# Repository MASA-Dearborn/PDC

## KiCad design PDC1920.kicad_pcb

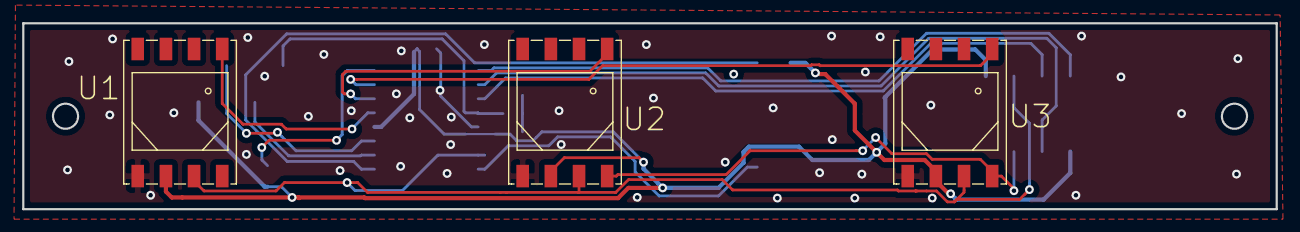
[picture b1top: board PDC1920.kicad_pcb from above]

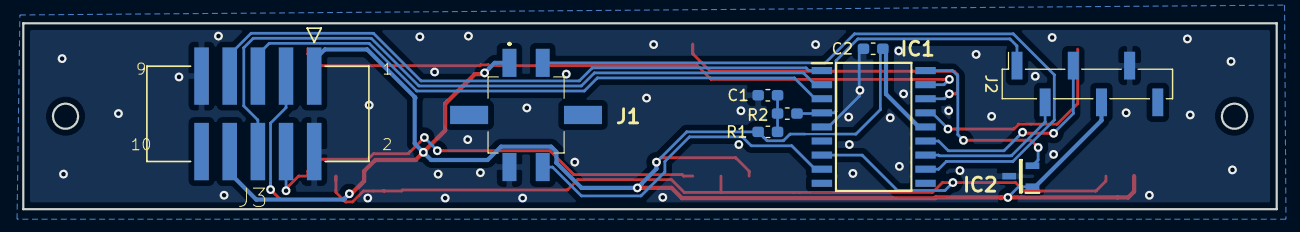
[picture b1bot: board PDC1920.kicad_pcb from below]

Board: 2 copper layers, 113.0 x 16.8 mm, 12 parts (9 on the bottom side), 17 nets.

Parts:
C1, C2: .1u; C_0603_1608Metric_Pad1.05x0.95mm_HandSolder
IC1: PIC16LF1826-I_SO; SOIC127P1030X265-18N
IC2: LM60CIM3_NOPB; SOT95P237X112-3N
J1: Conn_01x04; 37946364
J2: Conn_01x06; PinHeader_1x06_P2.54mm_Vertical_SMD_Pin1Right
J3: Conn_01x10_Male; 3M_N2510-6V0C-RB-WD
R1: 10k; R_0603_1608Metric_Pad1.05x0.95mm_HandSolder
R2: 1k; R_0603_1608Metric_Pad1.05x0.95mm_HandSolder
U1, U2, U3: PressureSensor

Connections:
+3V3: C2.1, IC1.14, IC2.1, J1.1, J2.4, J3.1, J3.8, R1.2, U1.2, U2.2, U3.2
GND: C1.2, C2.2, IC1.5, IC2.3, J1.2, J2.5, J3.2, J3.9, U1.1, U2.1, U3.1
ICSPCLK: IC1.12, J2.2
ICSPDAT: IC1.13, J2.3
MISO: IC1.7, J3.3, U1.3, U2.3, U3.3
unnamed: C1.1, R1.1, R2.2
SCLK: J3.4, U1.4, U2.4, U3.4
SS0: IC1.1, J3.7
SS1: IC1.2, J3.6
SS2: IC1.3, J3.5
SS3: IC1.15, U1.5
SS4: IC1.16, U2.5
SS5: IC1.17, U3.5
TempO: IC1.18, IC2.2
UART_RX: IC1.8, J1.4
UART_TX: IC1.11, J1.3
~MCLR: IC1.4, J2.1, R2.1

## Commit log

2020-01-25 Added PDC Files
